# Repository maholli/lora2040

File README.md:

# lora2040

Just playing with RP2040 w/ mram + SX1262 radio.

Will eventually reduce the size and add castellations for "mezzanine" style surface mounting.

# Example Software - Meshtastic RX
1. Open serial terminal ([can use chrome or edge with this link](https://googlechromelabs.github.io/serial-terminal/) if you don't already have a preferred serial terminal method)
   
2. Ctrl+e for paste-mode
3. Paste the following:
   ```python
   import time
   from machine import Pin, SPI
   # Uses the official micropython-lib lora sx1262 lib
   # https://github.com/micropython/micropython-lib/tree/master/micropython/lora
   from lora import SX1262
   
   # meshtastic default "LongFast" on default frequency slot 20
   lora_cfg = {
       "freq_khz": 906_875,
       "sf": 11,
       "bw": "250",  # kHz
       "coding_rate": 5,
       "preamble_len": 16,
       "output_power": 0,  # dBm
       # "syncword":0x2B, # SETTING SYNCWORD MUST BE DONE MANUALLY. SEE BELOW
       "rx_boost":True,
   }
      
   print("Initializing...")
   
   modem = SX1262(
       spi=SPI(0, baudrate=8_000_000, polarity=0, phase=0,
               sck=Pin(18), miso=Pin(16), mosi=Pin(19)),
       cs=Pin(17),
       reset=Pin(20),
       busy=Pin(21),
       dio1=Pin(25),
       dio2_rf_sw=True,
       dio3_tcxo_millivolts=2800,
       lora_cfg=lora_cfg,
   )
   
   # set custom meshtastic syncword
   modem._cmd(">BHH", 0x0D, 0x740, 0x24b4) # 0x2B == 0x24b4
   
   print("Listening...")
   
   print("[Packet payload, Timestamp (ms), SNR (dB*4), RSSI (dBm), Valid CRC]")
   while True:
       modem.recv()
   ```
4. Ctrl+d to run
5. Any packets received will be printed (note meshtastic payloads will still be encrypted):

-----

Reminders to myself:
- [x] Initial bring-up with Everspin MRAM
  - [ ] Avalanche MRAM
- [x] Full speed SX1262 interface
- [ ] Measure TX output power
- [ ] Measure RX sensitivity
- [ ] Maybe add an amp at some point?

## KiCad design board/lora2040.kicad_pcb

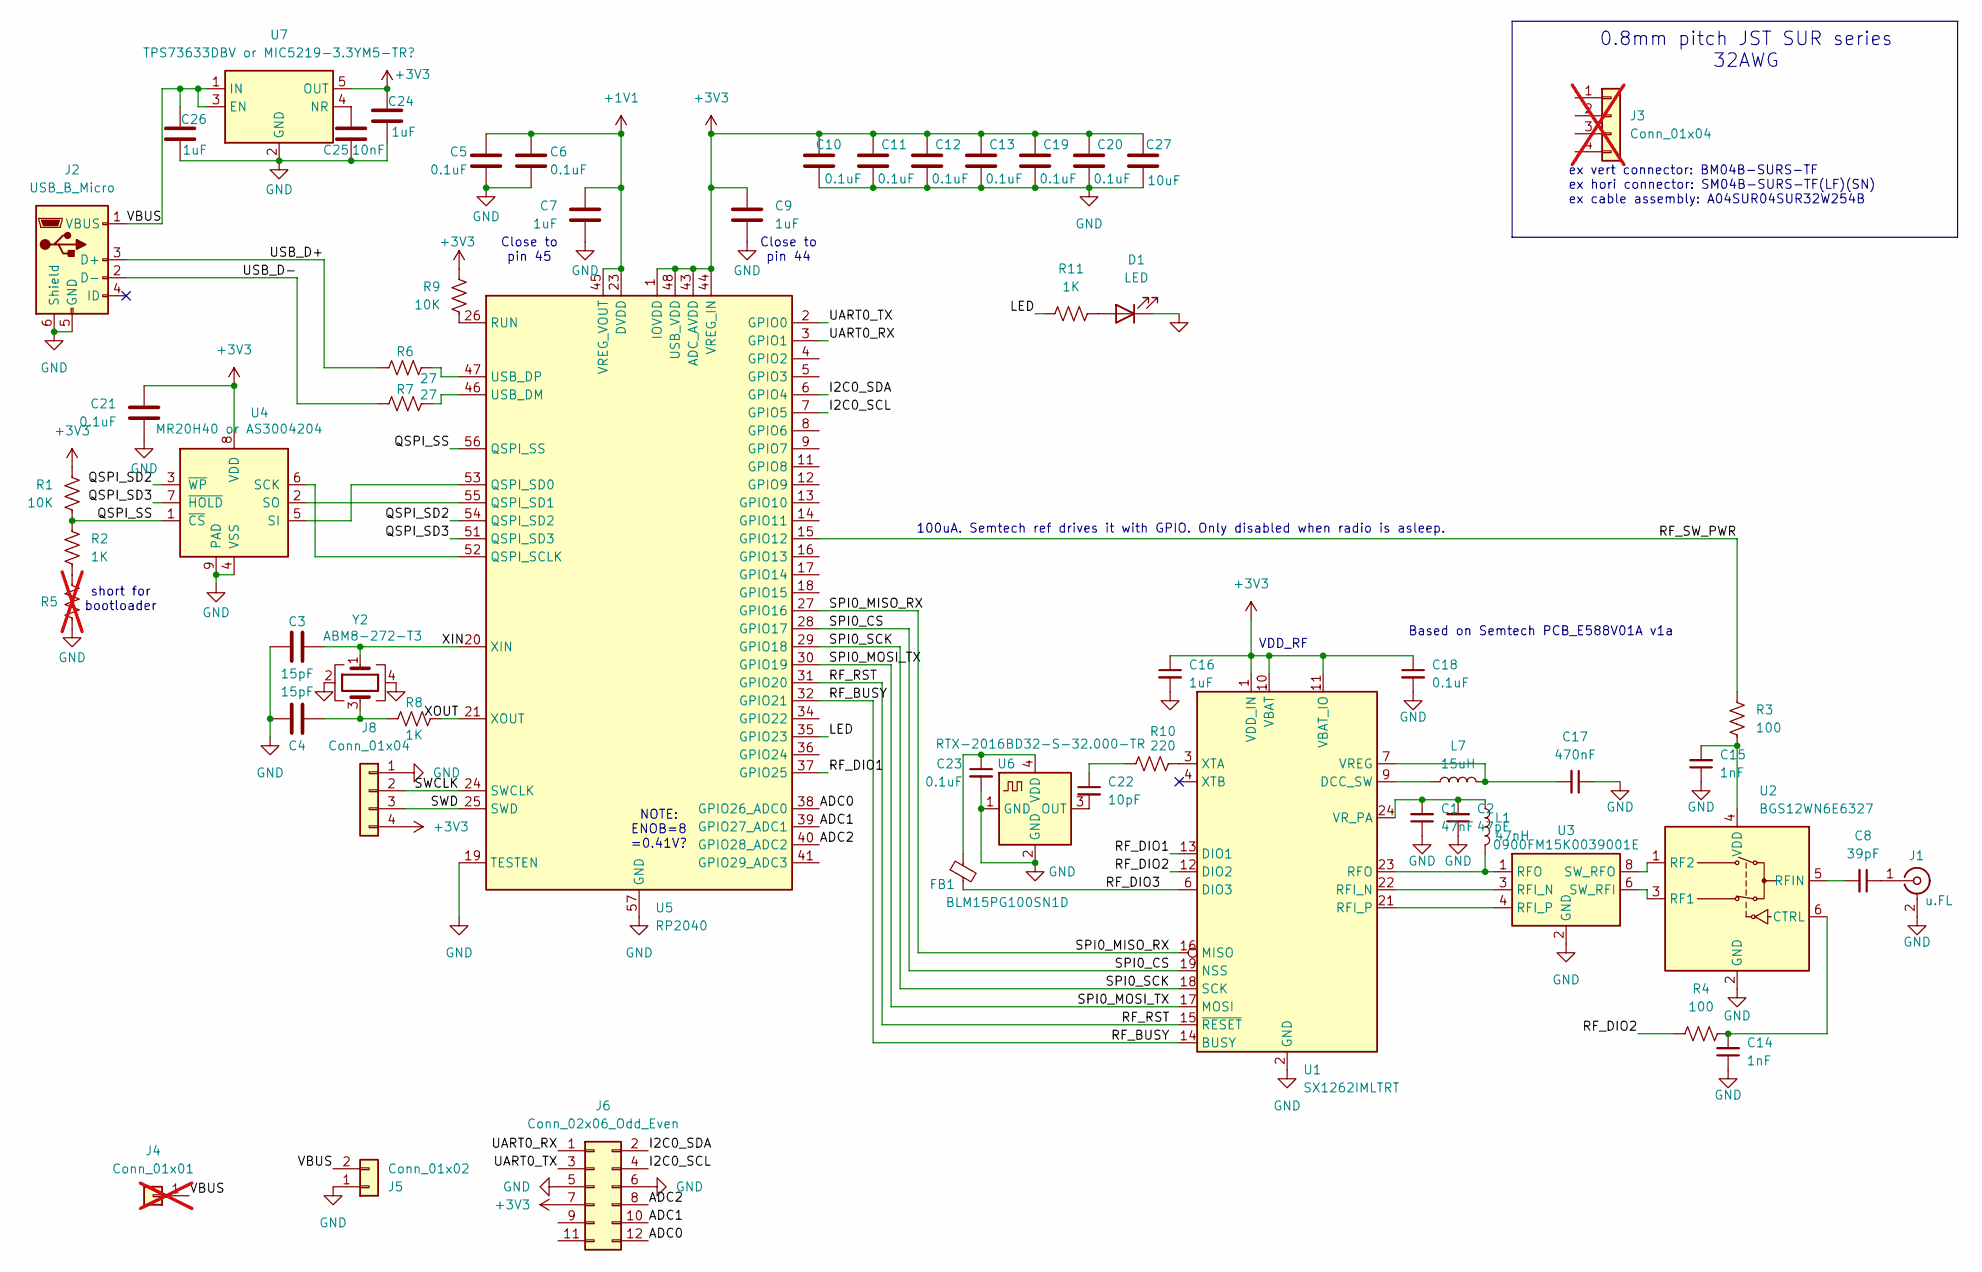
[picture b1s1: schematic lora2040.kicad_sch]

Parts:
C1: 47nF; sx126x_C_0201
C2: 47pF; sx126x_C_0201
C3, C4: 15pF; sx126x_C_0201
C5, C6, C10, C11, C12, C13, C18, C21, C23: 0.1uF; sx126x_C_0201
C7, C9, C24, C26: 1uF; C_0402_1005Metric
C8: 39pF; sx126x_C_0201
C14, C15: 1nF; sx126x_C_0201
C16: 1uF; sx126x_C_0402
C17: 470nF; sx126x_C_0402
C19, C20: 0.1uF; C_0402_1005Metric
C22: 10pF; sx126x_C_0201
C25: 10nF; C_0402_1005Metric
C27: 10uF; C_0402_1005Metric
D1: LED; LED_0402_1005Metric
FB1: BLM15PG100SN1D; sx126x_L_0402; Part Number BLM15PG100SN1D
J1: u.FL; U.FL_Hirose_U.FL-R-SMT-1_Vertical
J2: USB_B_Micro; USB_Micro-B_Molex-105017-0001
J3: Conn_01x04; JST_SUR_BM04B-SURS-TF_1x04-1MP_P0.80mm_Vertical; not fitted
J4: Conn_01x01; castellated_07mm; not fitted
J5: Conn_01x02; PinHeader_1x02_P1.00mm_Vertical
J6: Conn_02x06_Odd_Even; PinHeader_2x06_P1.00mm_Vertical
J8: Conn_01x04; PinHeader_1x04_P1.00mm_Vertical
L1: 47nH; sx126x_L_0402; Part Number LQW15AN47NJ00D
L7: 15uH; sx126x_L_0805; Part Number MLZ2012M150WT000
R1, R9: 10K; sx126x_R_0201
R2: 1K; R_0402_1005Metric
R3, R4: 100; sx126x_R_0201
R5: 0; R_0402_1005Metric; not fitted
R6, R7: 27; sx126x_R_0201
R8, R11: 1K; sx126x_R_0201
R10: 220; sx126x_R_0201
U1: SX1262IMLTRT; VQFN24_4X4MM_SX126x; Part Number SX1262IMLTRT
U2: BGS12WN6E6327; Infineon_PG-TSNP-6-10_0.7x1.1mm_0.7x1.1mm_P0.4mm; Part Number BGS12WN6E6327
U3: 0900FM15K0039001E; 0900FM15K0039; Part Number 0900FM15K0039001E
U4: MR20H40 or AS3004204; SON127P600X500X90-9N; Part Number AS3004204-0054X0PWAY
U5: RP2040; QFN-56-1EP_7x7mm_P0.4mm_EP3.2x3.2mm; Part Number SC0914
U6: RTX-2016BD32-S-32.000-TR; TXCO_2.0x1.6; Part Number RTX-2016BD32-S-32.000-TR
U7: TPS73633DBV or MIC5219-3.3YM5-TR?; SOT-23-5; Part Number MIC5219-3.3YM5-TR
Y2: ABM8-272-T3; Crystal_SMD_3225-4Pin_3.2x2.5mm; Part Number ABM8-272-T3

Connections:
+1V1: C5.2, C6.2, C7.2, U5.23 (DVDD), U5.45 (VREG_VOUT), U5.50 (DVDD)
+3V3: C9.2, C10.2, C11.2, C12.2, C13.2, C16.1, C18.1, C19.2, C20.2, C21.2, C24.2, C27.2, J6.7, J8.4, R1.2, R9.2, U1.1 (VDD_IN), U1.10 (VBAT), U1.11 (VBAT_IO), U4.8 (VDD), U5.1 (IOVDD), U5.10 (IOVDD), U5.22 (IOVDD), U5.33 (IOVDD), U5.42 (IOVDD), U5.43 (ADC_AVDD), U5.44 (VREG_IN), U5.48 (USB_VDD), U5.49 (IOVDD), U7.5 (OUT)
/ADC0: J6.12, U5.38 (GPIO26_ADC0)
/ADC1: J6.10, U5.39 (GPIO27_ADC1)
/ADC2: J6.8, U5.40 (GPIO28_ADC2)
/I2C0_SCL: J6.4, U5.7 (GPIO5)
/I2C0_SDA: J6.2, U5.6 (GPIO4)
/LED: R11.1, U5.35 (GPIO23)
/QSPI_SD2: U4.3 (~WP), U5.54 (QSPI_SD2)
/QSPI_SD3: U4.7 (~HOLD), U5.51 (QSPI_SD3)
/QSPI_SS: R1.1, R2.2, U4.1 (~CS), U5.56 (QSPI_SS)
/RF_BUSY: U1.14 (BUSY), U5.32 (GPIO21)
/RF_DIO1: U1.13 (DIO1), U5.37 (GPIO25)
/RF_DIO2: R4.1, U1.12 (DIO2)
/RF_DIO3: FB1.2, U1.6 (DIO3)
/RF_RST: U1.15 (~RESET), U5.31 (GPIO20)
/RF_SW_PWR: R3.2, U5.15 (GPIO12)
/SPI0_CS: U1.19 (NSS), U5.28 (GPIO17)
/SPI0_MISO_RX: U1.16 (MISO), U5.27 (GPIO16)
/SPI0_MOSI_TX: U1.17 (MOSI), U5.30 (GPIO19)
/SPI0_SCK: U1.18 (SCK), U5.29 (GPIO18)
/SWCLK: J8.2, U5.24 (SWCLK)
/SWD: J8.3, U5.25 (SWD)
/UART0_RX: J6.1, U5.3 (GPIO1)
/UART0_TX: J6.3, U5.2 (GPIO0)
/USB_D+: J2.3 (D+), R6.1
/USB_D-: J2.2 (D-), R7.1
/VBUS: C26.2, J2.1 (VBUS), J4.1, J5.2, U7.1 (IN), U7.3 (EN)
/XIN: C3.2, U5.20 (XIN), Y2.1
/XOUT: R8.2, U5.21 (XOUT)
GND: C1.1, C2.1, C3.1, C4.1, C5.1, C6.1, C7.1, C9.1, C10.1, C11.1, C12.1, C13.1, C14.1, C15.1, C16.2, C17.1, C18.2, C19.1, C20.1, C21.1, C23.2, C24.1, C25.1, C26.1, C27.1, D1.1 (K), J1.2 (Ext), J2.5 (GND), J2.6 (Shield), J5.1, J6.5, J6.6, J8.1, R5.1, U1.2 (GND), U1.5 (GND), U1.8 (GND), U1.20 (GND), U1.25 (GND), U2.2 (GND), U3.2 (GND), U3.5 (GND), U3.7 (GND), U3.9 (GND), U3.10 (GND), U4.4 (VSS), U4.9 (PAD), U5.19 (TESTEN), U5.57 (GND), U6.1 (GND), U6.2 (GND), U7.2 (GND), Y2.2, Y2.4
unnamed: C4.2, R8.1, Y2.3
unnamed: C22.1, R10.1
unnamed: D1.2 (A), R11.2
unnamed: C8.1, J1.1 (In)
unnamed: R2.1, R5.2
unnamed: L7.1, U1.9 (DCC_SW)
unnamed: U1.22 (RFI_N), U3.3 (RFI_N)
unnamed: U1.21 (RFI_P), U3.4 (RFI_P)
unnamed: L1.2, U1.23 (RFO), U3.1 (RFO)
unnamed: C17.2, L7.2, U1.7 (VREG)
unnamed: C1.2, C2.2, L1.1, U1.24 (VR_PA)
unnamed: R10.2, U1.3 (XTA)
unnamed: C14.2, R4.2, U2.6 (CTRL)
unnamed: U2.3 (RF1), U3.6 (SW_RFI)
unnamed: U2.1 (RF2), U3.8 (SW_RFO)
unnamed: C8.2, U2.5 (RFIN)
unnamed: C15.2, R3.1, U2.4 (VDD)
unnamed: U4.6 (SCK), U5.52 (QSPI_SCLK)
unnamed: U4.5 (SI), U5.53 (QSPI_SD0)
unnamed: U4.2 (SO), U5.55 (QSPI_SD1)
unnamed: R9.1, U5.26 (RUN)
unnamed: R7.2, U5.46 (USB_DM)
unnamed: R6.2, U5.47 (USB_DP)
unnamed: C22.2, U6.3 (OUT)
unnamed: C23.1, FB1.1, U6.4 (VDD)
unnamed: C25.2, U7.4 (NR)

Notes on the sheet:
0.8mm pitch JST SUR series 32AWG
ex vert connector: BM04B-SURS-TF ex hori connector: SM04B-SURS-TF(LF)(SN) ex cable assembly: A04SUR04SUR32W254B
NOTE: ENOB=8 =0.41V?
100uA. Semtech ref drives it with GPIO. Only disabled when radio is asleep.
Close to pin 45
VDD_RF
Close to pin 44
short for bootloader
Based on Semtech PCB_E588V01A v1a

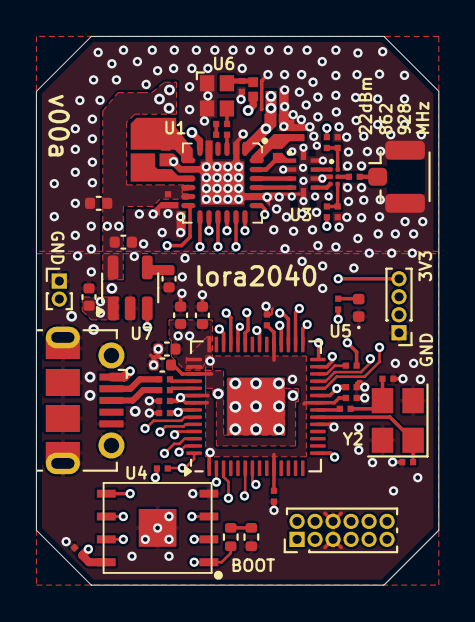
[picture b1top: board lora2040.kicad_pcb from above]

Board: 4 copper layers, 22.4 x 30.5 mm, 55 parts (0 on the bottom side), 57 nets.

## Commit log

2024-06-11 roughing in parts as I think of it
2024-06-16 added in sx1262 ref design
2024-06-16 about to switch to TXCO
2024-06-16 changed to TXCO
2024-06-16 seeing what castelations look like
2024-06-17 routing tests
2024-06-18 BOM clean up and routing
2024-06-18 v00a manufacturing files
2024-06-25 schematic cleanup and BOM
2024-07-03 gitignore
2024-07-03 readme
2024-07-03 typo
2024-07-04 add pic
2024-07-04 add micropython build files
2024-07-04 clean up temp files
2024-07-06 add lora libs to firmware build
2024-07-06 add example mp script to readme
